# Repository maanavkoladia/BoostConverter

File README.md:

# High-Efficiency Boost Converter for Electric Bike Motor

This project is a high-efficiency **24V to 48V boost converter** designed for an electric bike motor. Built using a **TI F280049C microcontroller**, the system delivers precise control and optimized power conversion for high-performance motor operation.

## Project Overview

- **Precise Control:**
  - Utilizes the **TI F280049C microcontroller** to implement high-resolution **PWM** and **ADC-based control loops**.
  - Enables accurate current sensing and precise **MOSFET switching** for efficient power conversion.

- **Custom PCB Design:**
  - Developed a custom PCB layout to minimize parasitic effects and optimize high-frequency power conversion.
  - Integrated essential components, including **gate drivers**, **protection circuits**, **current sensors**, and **DC power supplies**, for a compact and efficient design.

- **Advanced Hardware Design:**
  - Fabricated a custom bobbin-wound inductor to handle high power requirements.
  - Strategically arranged components to minimize **electromagnetic interference (EMI)** and improve system reliability.

## Implementation Highlights

- The boost converter effectively steps up voltage from 24V to 48V, powering an electric bike motor with high efficiency.
- High-resolution PWM ensures precise switching, while ADC-based feedback enables accurate current and voltage control.
- The design emphasizes efficiency and reliability, with advanced EMI mitigation strategies and robust circuit protection.

The **High-Efficiency Boost Converter** demonstrates a practical and scalable approach to power electronics for electric mobility applications.

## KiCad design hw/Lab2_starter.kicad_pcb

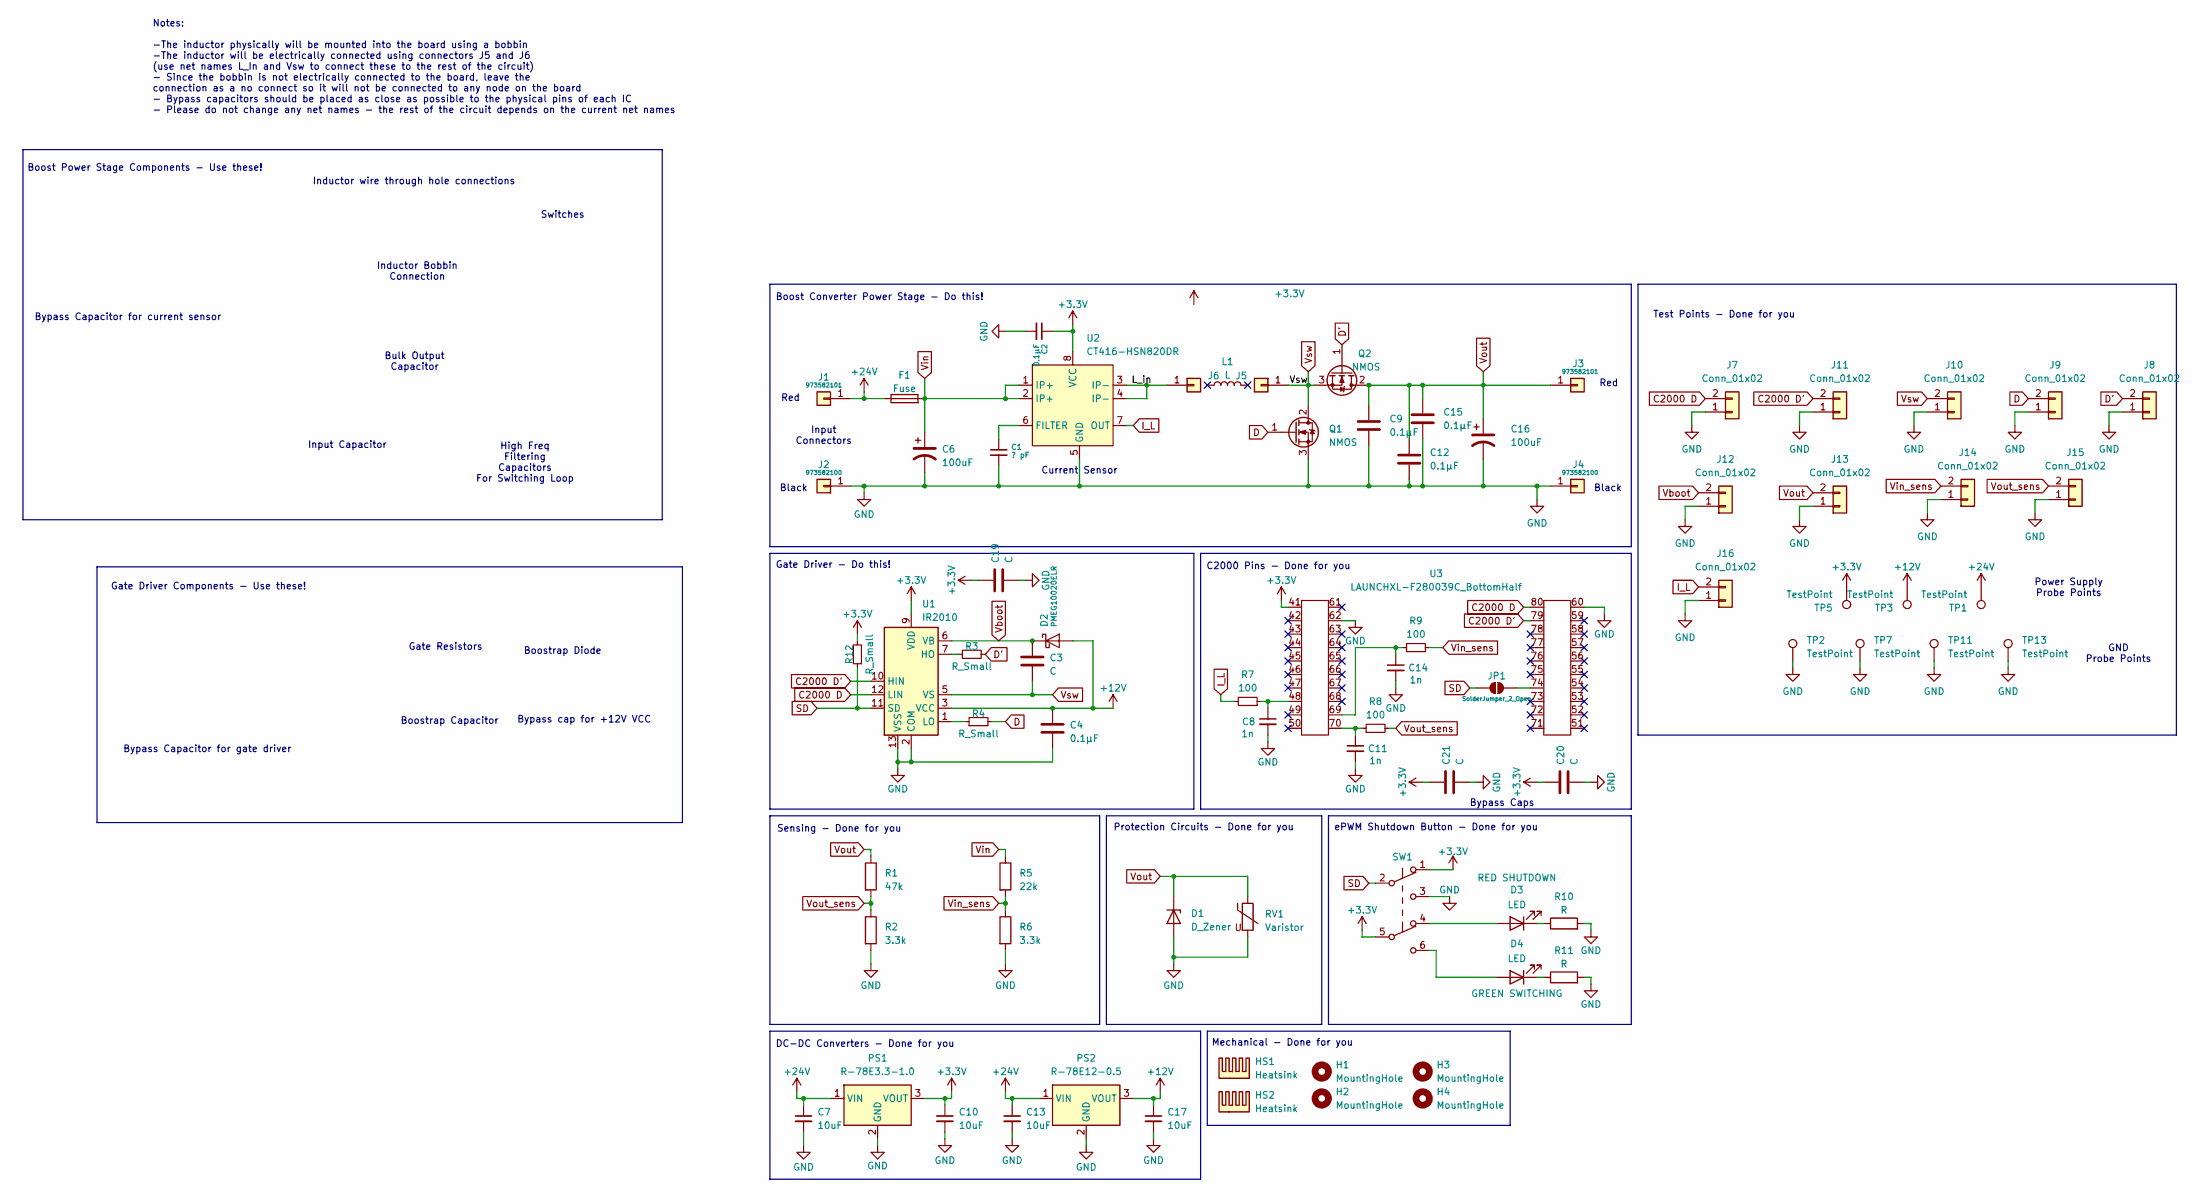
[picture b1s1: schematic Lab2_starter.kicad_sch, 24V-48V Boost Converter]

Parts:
C1: ? pF; C_0805_2012Metric
C2, C4, C9, C12, C15: 0.1μF; C_0805_2012Metric
C3, C19, C20, C21: C; C_0805_2012Metric
C6, C16: 100uF; 16PX2200MEFC10X20
C7, C10, C13, C17: 10uF; C_0805_2012Metric
C8, C11, C14: 1n; C_0805_2012Metric
D1: D_Zener; 1.5KE75A
D2: PMEG10020ELR; Nexperia_CFP3_SOD-123W
D3, D4: LED; WL-SMRW_1206_REC
F1: Fuse; 03540101ZXGY
H1, H2, H3, H4: MountingHole; MountingHole_3.2mm_M3
HS1, HS2: Heatsink; 513102B02500G
J1, J3: 973582101
J2, J4: 973582100
J5, J6: Conn_01x01; Inductor_wire_conn
J7, J8, J9, J10, J11, J12, J13, J14, J15, J16: Conn_01x02; TP
JP1: SolderJumper_2_Open; SolderJumper-2_P1.3mm_Open_RoundedPad1.0x1.5mm
L1: L; Inductor
PS1: R-78E3.3-1.0; PARTREV 6
PS2: R-78E12-0.5; R-78E-0.5_RCP
Q1, Q2: NMOS; TO-220-3_Vertical
R1: 47k; R_0805_2012Metric
R2, R6: 3.3k; R_0805_2012Metric
R3, R4, R12: R_Small; R_0805_2012Metric
R5: 22k; R_0805_2012Metric
R7, R8, R9: 100; R_0805_2012Metric
R10, R11: R; R_0805_2012Metric
RV1: Varistor; V100ZA15P
SW1: SW_Push_DPDT; SLW1116297AD
TP1, TP2, TP3, TP5, TP7, TP11, TP13: TestPoint; TestPoint_Loop_D1.80mm_Drill1.0mm_Beaded
U1: IR2010; 1-2199298-3
U2: CT416-HSN820DR; SOIC-8_3.9x4.9mm_P1.27mm
U3: LAUNCHXL-F280039C_BottomHalf; LAUNCHXL-F280049C_BottomHalf

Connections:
+3.3V: C2.1, C10.1, C19.1, C20.1, C21.1, PS1.3 (VOUT), R12.2, SW1.1 (A), SW1.5 (B), TP5.1, U1.9 (VDD), U2.8 (VCC), U3.41
+12V: C4.1, C17.1, D2.2 (A), PS2.3 (VOUT), TP3.1, U1.3 (VCC)
+24V: C7.1, C13.1, F1.1, J1.1, PS1.1 (VIN), PS2.1 (VIN), TP1.1
/L_in: J6.1, U2.3 (IP-), U2.4 (IP-)
C2000 D: J7.2, U1.12 (LIN), U3.80
C2000 D': J11.2, U1.10 (HIN), U3.79
D: J9.2, Q1.1 (G), R4.2
D': J8.2, Q2.1 (G), R3.2
GND: C1.2, C2.2, C4.2, C6.2, C7.2, C8.2, C9.2, C10.2, C11.2, C12.2, C13.2, C14.2, C15.2, C16.2, C17.2, C19.2, C20.2, C21.2, D1.2 (A), J2.1, J4.1, J7.1, J8.1, J9.1, J10.1, J11.1, J12.1, J13.1, J14.1, J15.1, J16.1, PS1.2 (GND), PS2.2 (GND), Q1.3 (S), R2.2, R6.2, R10.2, R11.2, RV1.2, SW1.3 (C), TP2.1, TP7.1, TP11.1, TP13.1, U1.2 (COM), U1.13 (VSS), U2.5 (GND), U3.60, U3.62
I_L: J16.2, R7.2, U2.7 (OUT)
unnamed: C8.1, R7.1, U3.48
unnamed: C11.1, R8.1, U3.70
unnamed: C14.1, R9.1, U3.69
unnamed: D3.2 (A), SW1.4 (A)
unnamed: D3.1 (K), R10.1
unnamed: D4.2 (A), SW1.6 (C)
unnamed: D4.1 (K), R11.1
unnamed: JP1.1 (A), U3.74
unnamed: R3.1, U1.7 (HO)
unnamed: R4.1, U1.1 (LO)
unnamed: C1.1, U2.6 (FILTER)
SD: JP1.2 (B), R12.1, SW1.2 (B), U1.11 (SD)
Vboot: C3.1, D2.1 (K), J12.2, U1.6 (VB)
Vin: C6.1, F1.2, R5.1, U2.1 (IP+), U2.2 (IP+)
Vin_sens: J14.2, R5.2, R6.1, R9.2
Vout: C9.1, C12.1, C15.1, C16.1, D1.1 (K), J3.1, J13.2, Q2.2 (D), R1.1, RV1.1
Vout_sens: J15.2, R1.2, R2.1, R8.2
Vsw: C3.2, J5.1, J10.2, Q1.2 (D), Q2.3 (S), U1.5 (VS)

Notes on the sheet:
High Freq Filtering Capacitors For Switching Loop
Inductor wire through hole connections
Input Connectors
Sensing - Done for you
Protection Circuits - Done for you
Input Capacitor
Test Points - Done for you
Bypass cap for +12V VCC
Black
Mechanical - Done for you
Red
Bulk Output Capacitor
Power Supply Probe Points
Boostrap Capacitor
ePWM Shutdown Button - Done for you
Notes: -The inductor physically will be mounted into the board using a bobbin -The inductor will be electrically connected using connectors J5 and J6 (use net names L_In and Vsw to connect these to the rest of the circuit) - Since the bobbin is not electrically connected to the board, leave the con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
Gate Driver - Do this!
Current Sensor
DC-DC Converters - Done for you
Boost Power Stage Components - Use these!
Gate Resistors
C2000 Pins - Done for you
Boostrap Diode
Bypass Capacitor for current sensor
Inductor Bobbin Connection
Switches
Bypass Capacitor for gate driver
Gate Driver Components - Use these!
GND Probe Points
Bypass Caps
Boost Converter Power Stage - Do this!

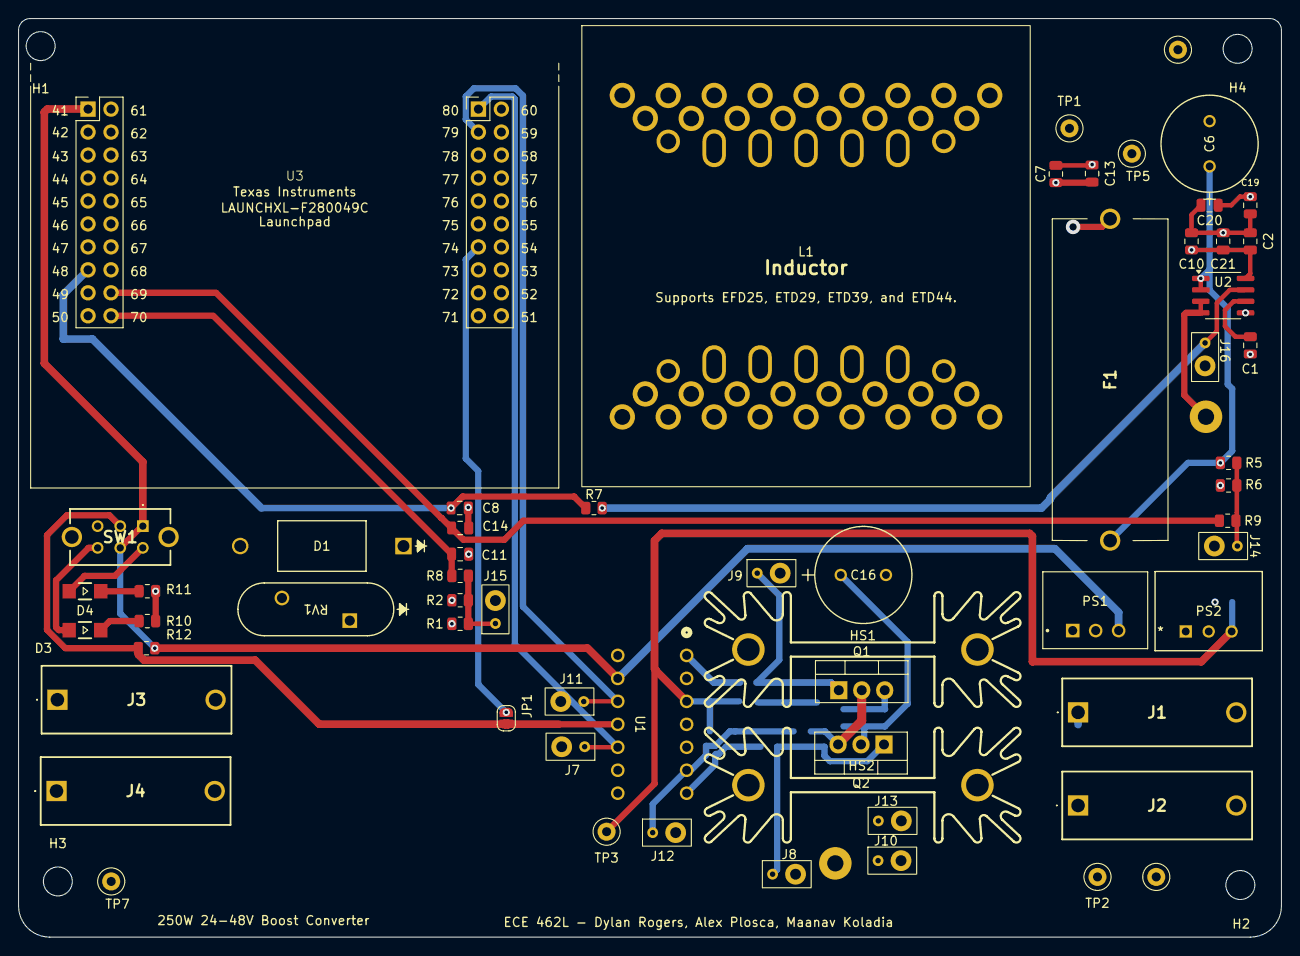
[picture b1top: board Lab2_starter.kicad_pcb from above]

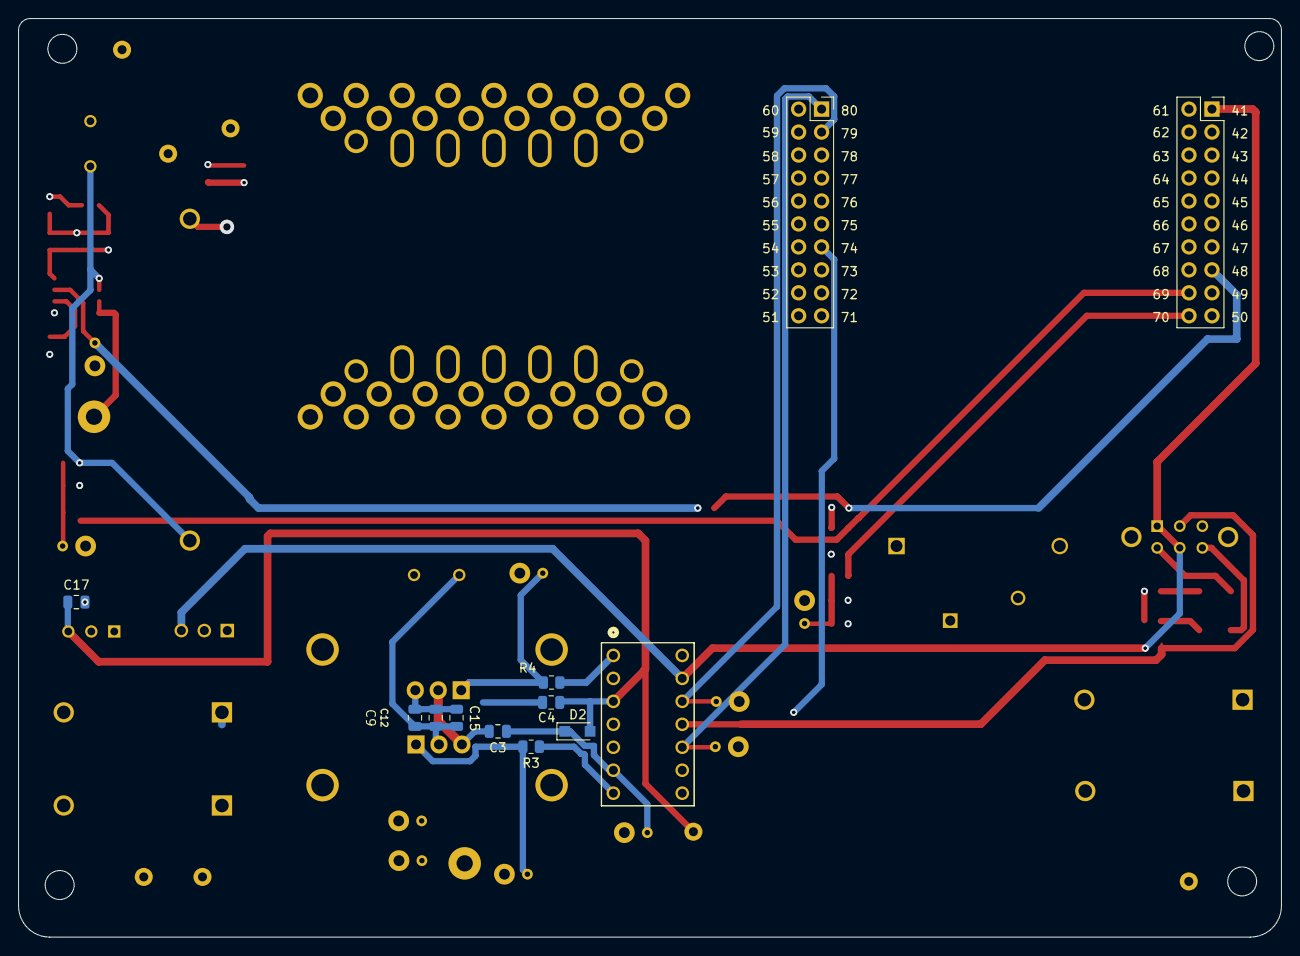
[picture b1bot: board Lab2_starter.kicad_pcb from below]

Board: 4 copper layers, 139.7 x 101.6 mm, 76 parts (10 on the bottom side), 28 nets.

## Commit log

2024-12-08 first
2024-12-08 testing

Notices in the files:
parts and their libraries:
Copyright 2016 Accelerated Designs. All rights reserved.
